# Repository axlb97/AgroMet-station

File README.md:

# AgroMet-station
Estación metereológica modular con comunicación inalámbrica a traves de modulos Xbee.

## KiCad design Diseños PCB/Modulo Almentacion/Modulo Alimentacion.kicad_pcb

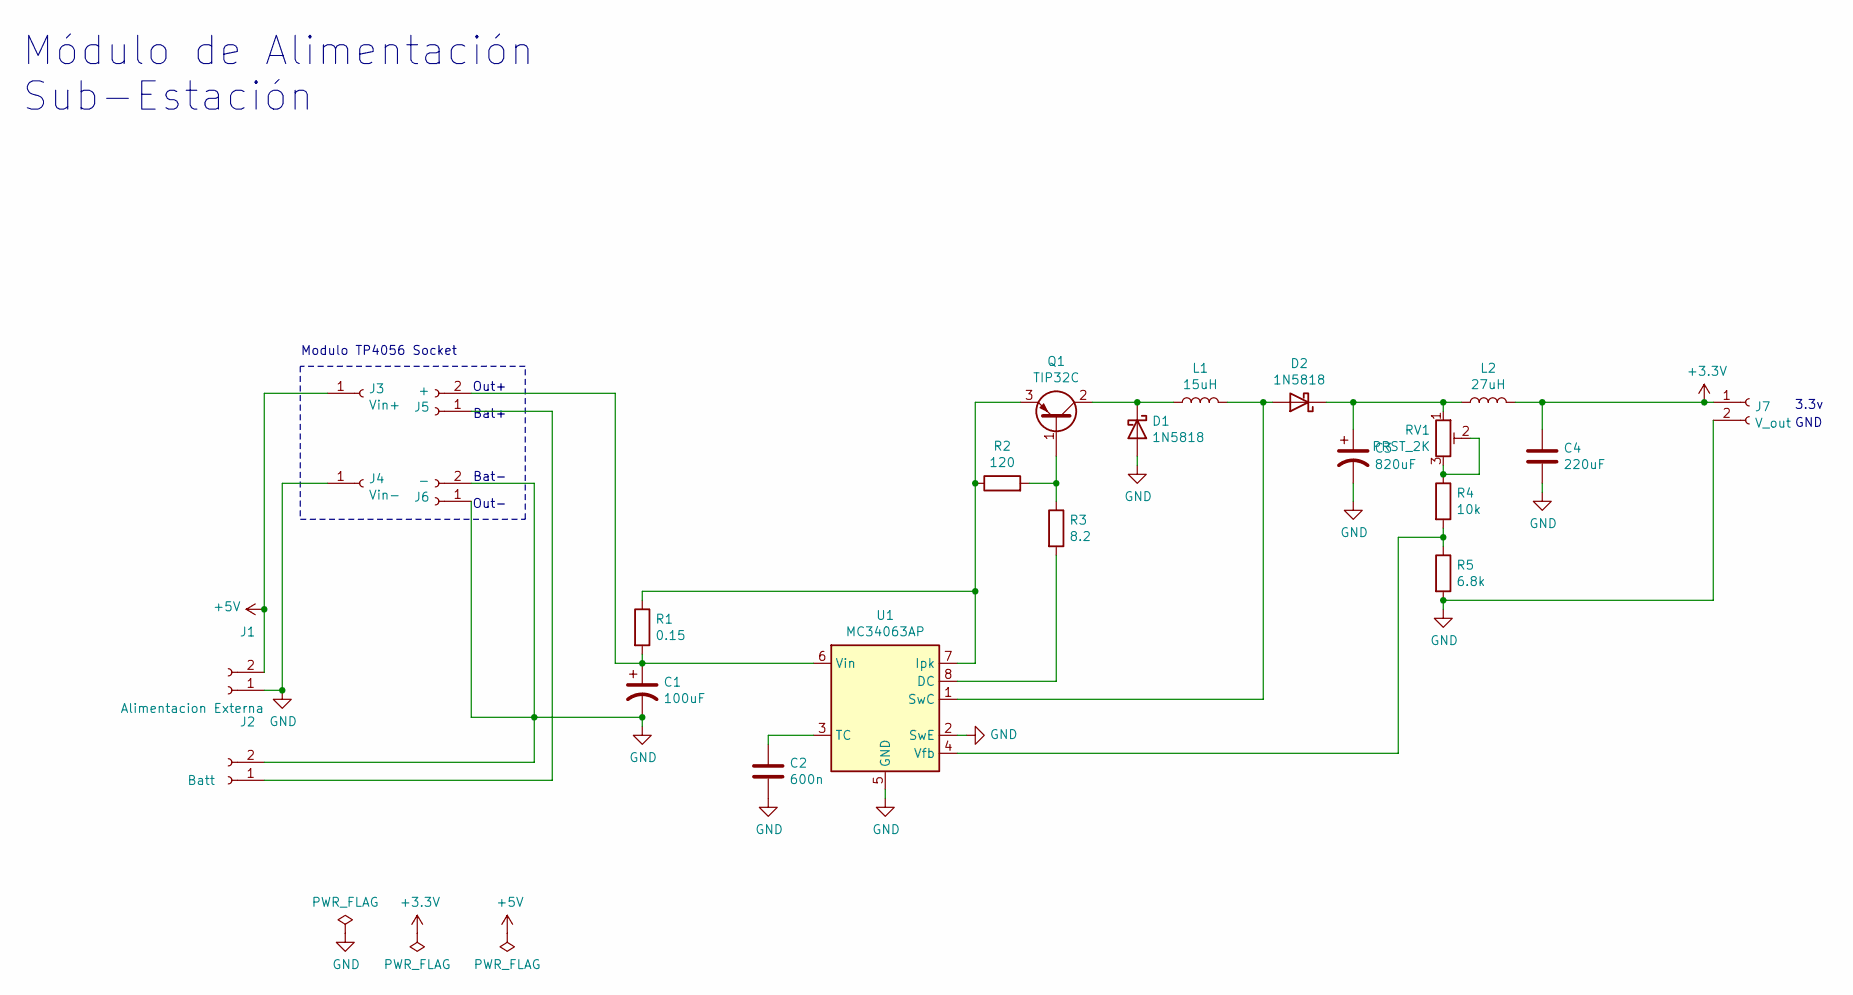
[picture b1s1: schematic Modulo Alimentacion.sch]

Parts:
C1: 100uF; CP_Radial_D6.3mm_P2.50mm
C2: 600n; C_Disc_D6.0mm_W2.5mm_P5.00mm
C3: 820uF; CP_Radial_D6.3mm_P2.50mm
C4: 220uF; C_Disc_D6.0mm_W2.5mm_P5.00mm
D1, D2: 1N5818; D_DO-41_SOD81_P10.16mm_Horizontal
J1: Alimentacion Externa; TerminalBlock_Phoenix_MKDS-1,5-2-5.08_1x02_P5.08mm_Horizont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
J2: Batt; BatteryHolder_Keystone_1042_1x18650
J3: Vin+; PinHeader_1x01_P2.54mm_Vertical
J4: Vin-; PinHeader_1x01_P2.54mm_Vertical
J5: +; PinHeader_1x02_P2.54mm_Vertical
J6: -; PinHeader_1x02_P2.54mm_Vertical
J7: V_out; TerminalBlock_Phoenix_MKDS-1,5-2-5.08_1x02_P5.08mm_Horizont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
L1: 15uH; L_Axial_L5.3mm_D2.2mm_P7.62mm_Horizontal_Vishay_IM-1
L2: 27uH; L_Axial_L5.3mm_D2.2mm_P7.62mm_Horizontal_Vishay_IM-1
Q1: TIP32C; TO-220-3_Vertical
R1: 0.15; R_Axial_DIN0207_L6.3mm_D2.5mm_P7.62mm_Horizontal
R2: 120; R_Axial_DIN0207_L6.3mm_D2.5mm_P7.62mm_Horizontal
R3: 8.2; R_Axial_DIN0207_L6.3mm_D2.5mm_P7.62mm_Horizontal
R4: 10k; R_Axial_DIN0207_L6.3mm_D2.5mm_P7.62mm_Horizontal
R5: 6.8k; R_Axial_DIN0207_L6.3mm_D2.5mm_P7.62mm_Horizontal
RV1: PRST_2K; Potentiometer_Bourns_3296Y_Vertical
U1: MC34063AP; DIP-8_W7.62mm

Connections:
+3V3: C4.1, J7.1, L2.2
+5V: J1.2, J3.1
GND: C1.2, C2.2, C3.2, C4.2, D1.2 (A), J1.1, J2.2, J4.1, J6.1, J6.2, J7.2, R5.2, U1.2 (SwE), U1.5 (GND)
unnamed: C1.1, J5.2, R1.2, U1.6 (Vin)
unnamed: C2.1, U1.3 (TC)
unnamed: C3.1, D2.1 (K), L2.1, RV1.1
unnamed: D1.1 (K), L1.1, Q1.2 (C)
unnamed: D2.2 (A), L1.2, U1.1 (SwC)
unnamed: J2.1, J5.1
unnamed: Q1.1 (B), R2.2, R3.1
unnamed: Q1.3 (E), R1.1, R2.1, U1.7 (Ipk)
unnamed: R3.2, U1.8 (DC)
unnamed: R4.1, RV1.2, RV1.3
unnamed: R4.2, R5.1, U1.4 (Vfb)

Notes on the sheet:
Módulo de Alimentación Sub-Estación
Bat+
Out+
Bat-
Out-
Modulo TP4056 Socket
GND
3.3v

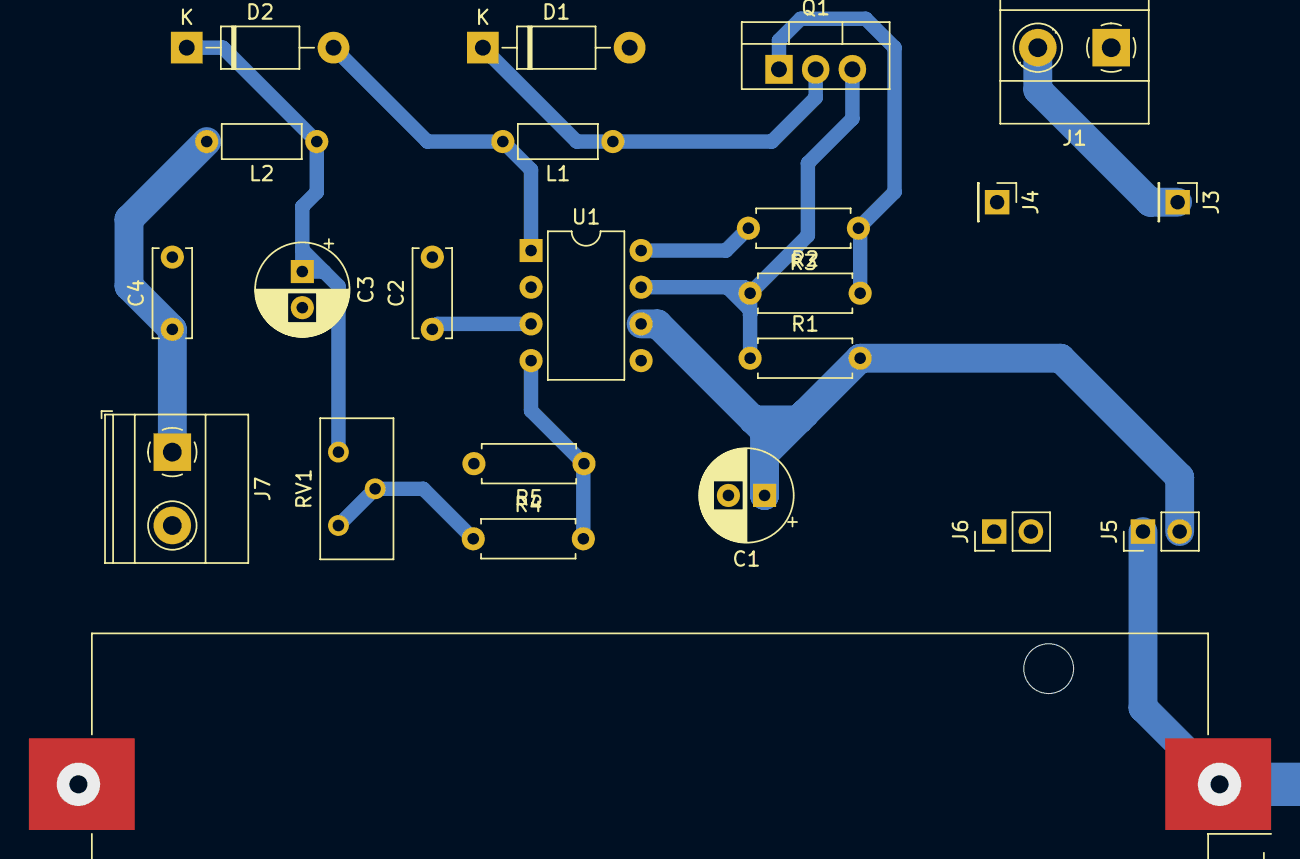
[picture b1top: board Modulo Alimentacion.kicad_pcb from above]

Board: 2 copper layers, 23 parts (0 on the bottom side), 14 nets.

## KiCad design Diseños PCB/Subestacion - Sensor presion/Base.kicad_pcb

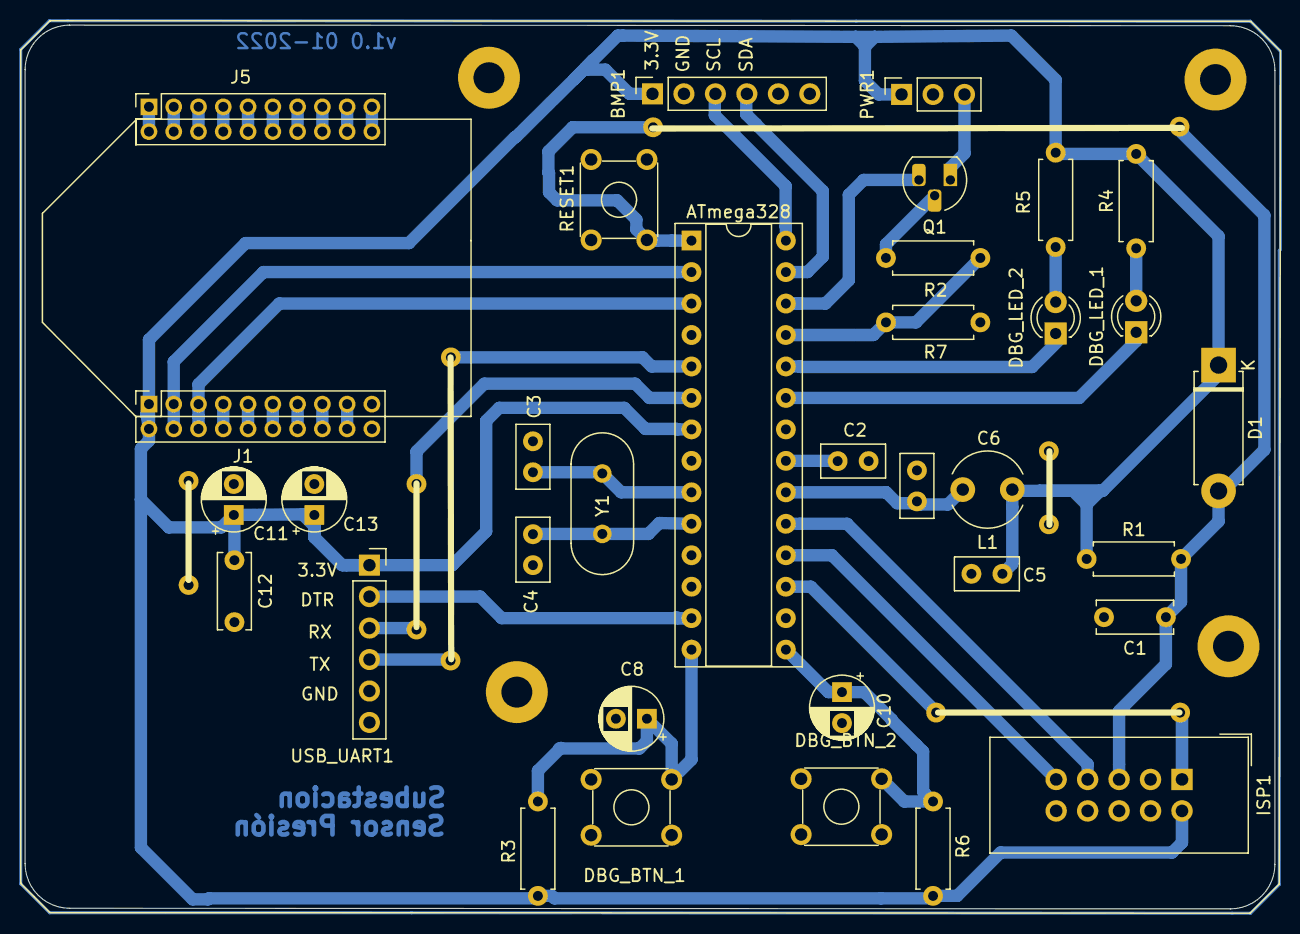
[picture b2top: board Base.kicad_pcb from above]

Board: 2 copper layers, 100.9 x 71.3 mm, 50 parts (0 on the bottom side), 43 nets.

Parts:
 : MountingHole_2.5mm_Pad
 #2,  #3,  #4: MountingHole_2.5mm_Pad
 #5,  #6,  #7,  #8,  #9,  #10,  #11,  #12,  #13,  #14,  #15,  #16: SolderWirePad_1x01_Drill0.8mm
ATmega328: ATmega328P-PU; DIP-28_W7.62mm_Socket
BMP1: Conn_01x06_Female; PinSocket_1x06_P2.54mm_Vertical
C1: 100n; C_Disc_D6.0mm_W2.5mm_P5.00mm
C2, C3, C4, C5, C6: 100n; C_Disc_D5.0mm_W2.5mm_P2.50mm
C8, C10, C11: 1u; CP_Radial_D5.0mm_P2.50mm
C12: 8.2p; C_Disc_D6.0mm_W2.5mm_P5.00mm
C13: 10u; CP_Radial_D5.0mm_P2.50mm
D1: D; D_5W_P10.16mm_Horizontal
DBG_BTN_1, DBG_BTN_2: SW_Push; SW_TH_Tactile_Omron_B3F-10xx
DBG_LED_1: DBG_LED_1; LED_D3.0mm_Clear
DBG_LED_2: DBG_LED_2; LED_D3.0mm_Clear
ISP1: Conn_ISP; IDC-Header_2x05_P2.54mm_Vertical
J1: Conn_XbeeS3_a; PinSocket_2x10_P2.00mm_Vertical
J5: Conn_XbeeS3_b; PinSocket_2x10_P2.00mm_Vertical
L1: 10u; L_Radial_D6.0mm_P4.00mm
PWR1: Conn_01x03_Male; PinSocket_1x03_P2.54mm_Vertical
Q1: Q_NMOS_DSG; TO-92L_HandSolder
R1: 47K; R_Axial_DIN0207_L6.3mm_D2.5mm_P7.62mm_Horizontal
R2, R7: R; R_Axial_DIN0207_L6.3mm_D2.5mm_P7.62mm_Horizontal
R3, R6: 10k; R_Axial_DIN0207_L6.3mm_D2.5mm_P7.62mm_Horizontal
R4, R5: 1k; R_Axial_DIN0207_L6.3mm_D2.5mm_P7.62mm_Horizontal
RESET1: SW_RESET; SW_TH_Tactile_Omron_B3F-10xx
USB_UART1: Conn_USB-UART-conv; PinSocket_1x06_P2.54mm_Vertical
Y1: Crystal; Crystal_HC49-4H_Vertical

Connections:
+3V3: ATmega328.7, BMP1.1, C5.2, C11.1, C12.1, C13.1, D1.1, ISP1.2, J1.1, J1.2, L1.1, PWR1.1, R1.1, R3.1, R4.1, R5.1, R6.1, USB_UART1.1
BMP_SCL: ATmega328.28, BMP1.3
BMP_SDA: ATmega328.27, BMP1.4
Bat_sense: ATmega328.25, R2.2, R7.1
DBG_BTN_1: ATmega328.14, C8.1, DBG_BTN_1.2, R3.2
DBG_BTN_2: ATmega328.15, C10.1, DBG_BTN_2.2, R6.2
DBG_LED_1: ATmega328.23, DBG_LED_1.1
DBG_LED_2: ATmega328.24, DBG_LED_2.1
GND: #5.1, #6.1, #11.1, #12.1, ATmega328.8, ATmega328.22, BMP1.2, C1.2, C2.1, C3.1, C4.1, C5.1, C6.2, C8.2, C10.2, C11.2, C12.2, C13.2, DBG_BTN_1.1, DBG_BTN_2.1, ISP1.10, J1.19, J1.20, PWR1.2, R7.2, RESET1.1, USB_UART1.5
MISO: ATmega328.18, ISP1.9
MOSI: #9.1, #10.1, ATmega328.17, ISP1.1
unnamed: ATmega328.9, C3.2, Y1.1
unnamed: ATmega328.10, C4.2, Y1.2
unnamed: ATmega328.20, C6.1, L1.2
unnamed: ATmega328.21, C2.2
unnamed: DBG_LED_1.2, R4.2
unnamed: DBG_LED_2.2, R5.2
unnamed: J1.7, J1.8
unnamed: J1.9, J1.10
unnamed: J1.11, J1.12
unnamed: J1.13, J1.14
unnamed: J1.15, J1.16
unnamed: J1.17, J1.18
unnamed: J5.1, J5.2
unnamed: J5.3, J5.4
unnamed: J5.5, J5.6
unnamed: J5.7, J5.8
unnamed: J5.9, J5.10
unnamed: J5.11, J5.12
unnamed: J5.13, J5.14
unnamed: J5.15, J5.16
unnamed: J5.17, J5.18
unnamed: J5.19, J5.20
unnamed: Q1.2, R2.1
RST: #7.1, #8.1, ATmega328.1, C1.1, D1.2, ISP1.5, R1.2, RESET1.2
SCK: ATmega328.19, ISP1.7
USB_DTR: ATmega328.13, USB_UART1.2
USB_RX_DATA-IN: #13.1, ATmega328.6, USB_UART1.3
USB_TX_DATA-OUT: #16.1, ATmega328.5, USB_UART1.4
Xbee_RX_DATA-IN: ATmega328.3, J1.5, J1.6
Xbee_TX_DATA-OUT: ATmega328.2, J1.3, J1.4
bat_in: PWR1.3, Q1.1
sense_en: ATmega328.26, Q1.3

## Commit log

2022-01-19 Subir Version 1.0
